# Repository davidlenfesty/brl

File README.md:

# brl

A poorly-designed resistive load.

I needed a resistive load to discharge some old LiPos for disposal, so I made this.
Designed with 90% parts on hand, so not exactly optimal or what I would want from a good
version.

Just adjust the pot to set a VREF and use an appropriately ranged shunt resistor to set your current.

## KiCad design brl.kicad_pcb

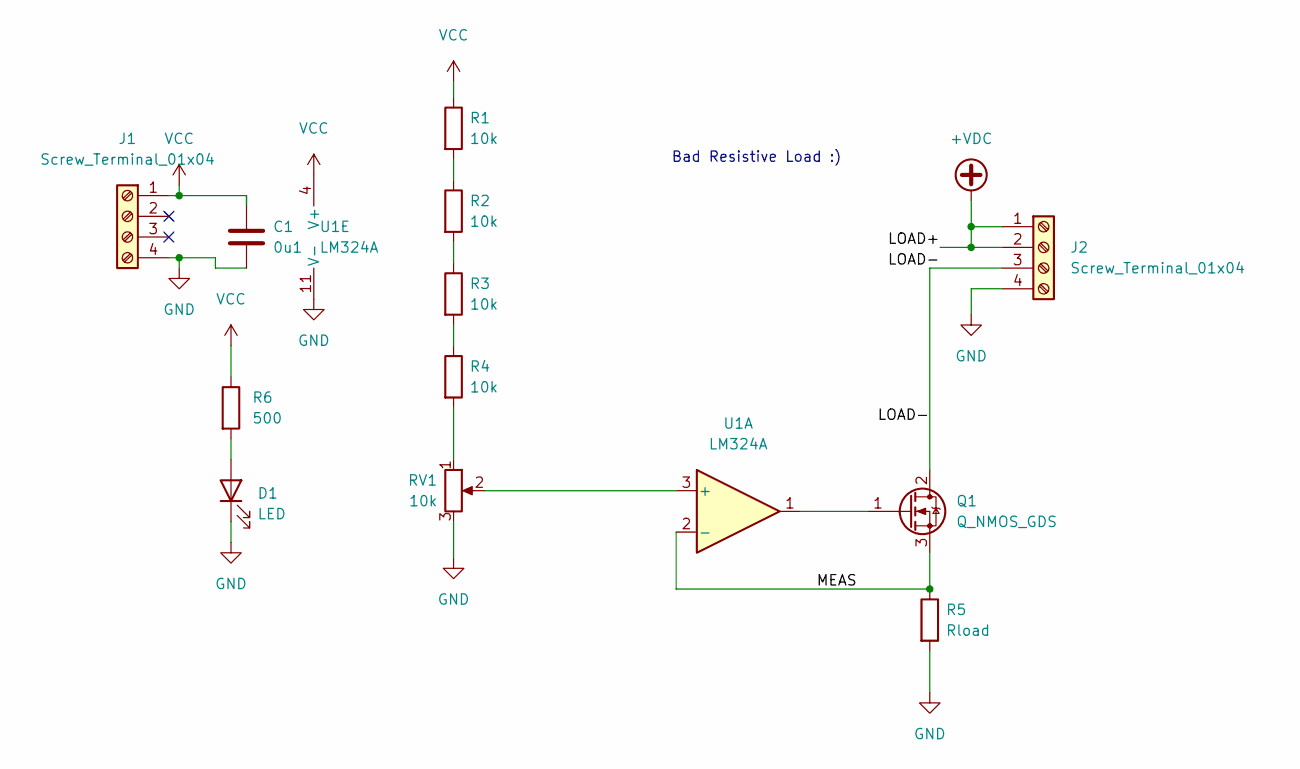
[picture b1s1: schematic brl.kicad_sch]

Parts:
C1: 0u1; C_0603_1608Metric
D1: LED; LED_0603_1608Metric_Pad1.05x0.95mm_HandSolder
J1, J2: Screw_Terminal_01x04; O_Shore_OSTTC042162
Q1: Q_NMOS_GDS; TO-220-3_Vertical
R1, R2, R3, R4: 10k; R_0805_2012Metric
R5: Rload; R_Axial_Power_L48.0mm_W12.5mm_P55.88mm
R6: 500; R_0805_2012Metric
RV1: 10k; Potentiometer_Bourns_3266Y_Vertical
U1: LM324A; DIP-14_W7.62mm_LongPads

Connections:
+VDC: J2.1, J2.2
/LOAD-: J2.3, Q1.2 (D)
/MEAS: Q1.3 (S), R5.1, U1.2 (-)
GND: C1.2, D1.1 (K), J1.4, J2.4, R5.2, RV1.3, U1.11 (V-)
unnamed: D1.2 (A), R6.2
unnamed: Q1.1 (G), U1.1
unnamed: R1.2, R2.1
unnamed: R2.2, R3.1
unnamed: R3.2, R4.1
unnamed: R4.2, RV1.1
unnamed: RV1.2, U1.3 (+)
VCC: C1.1, J1.1, R1.1, R6.1, U1.4 (V+)

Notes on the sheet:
Bad Resistive Load :)

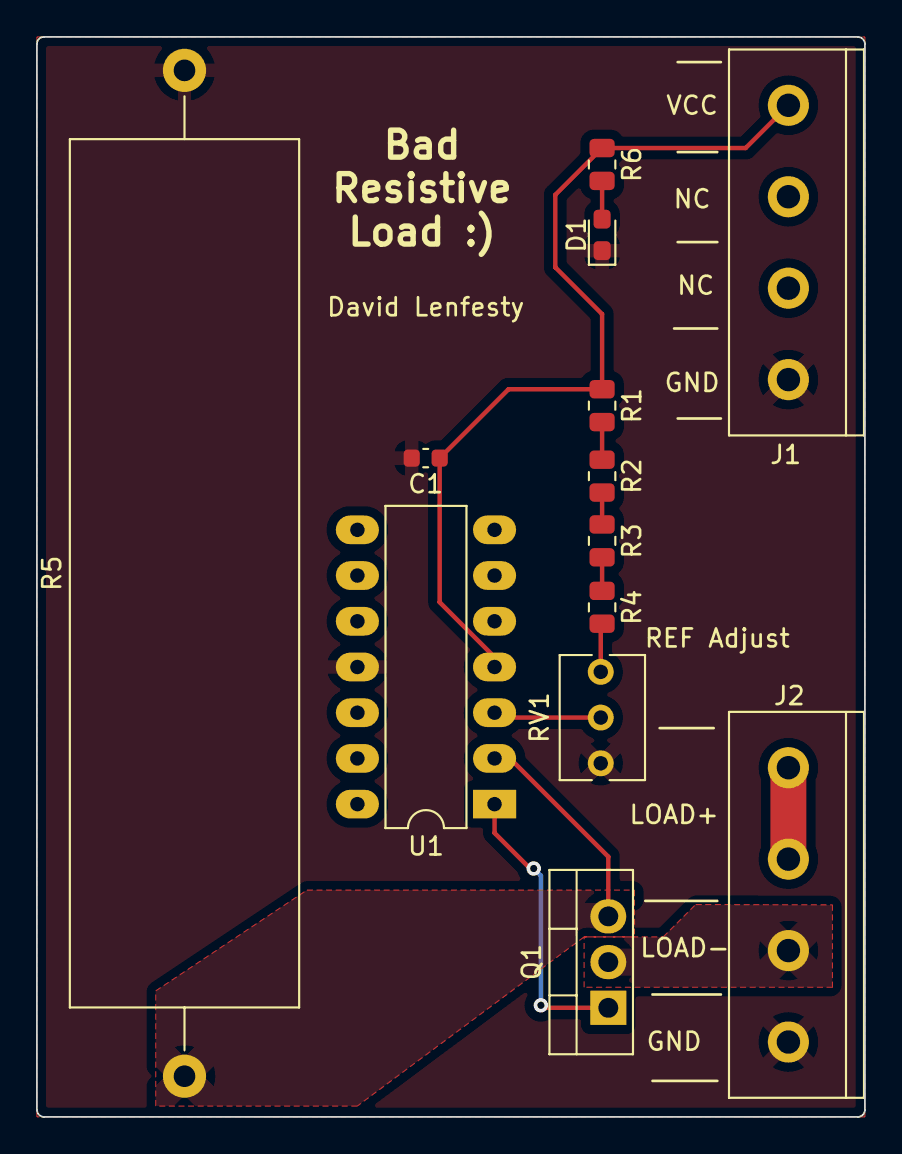
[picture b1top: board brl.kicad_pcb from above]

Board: 2 copper layers, 46.0 x 60.0 mm, 13 parts (0 on the bottom side), 12 nets.

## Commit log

2022-03-20 Created
2022-03-20 added silkscreen bits
2022-03-21 README
